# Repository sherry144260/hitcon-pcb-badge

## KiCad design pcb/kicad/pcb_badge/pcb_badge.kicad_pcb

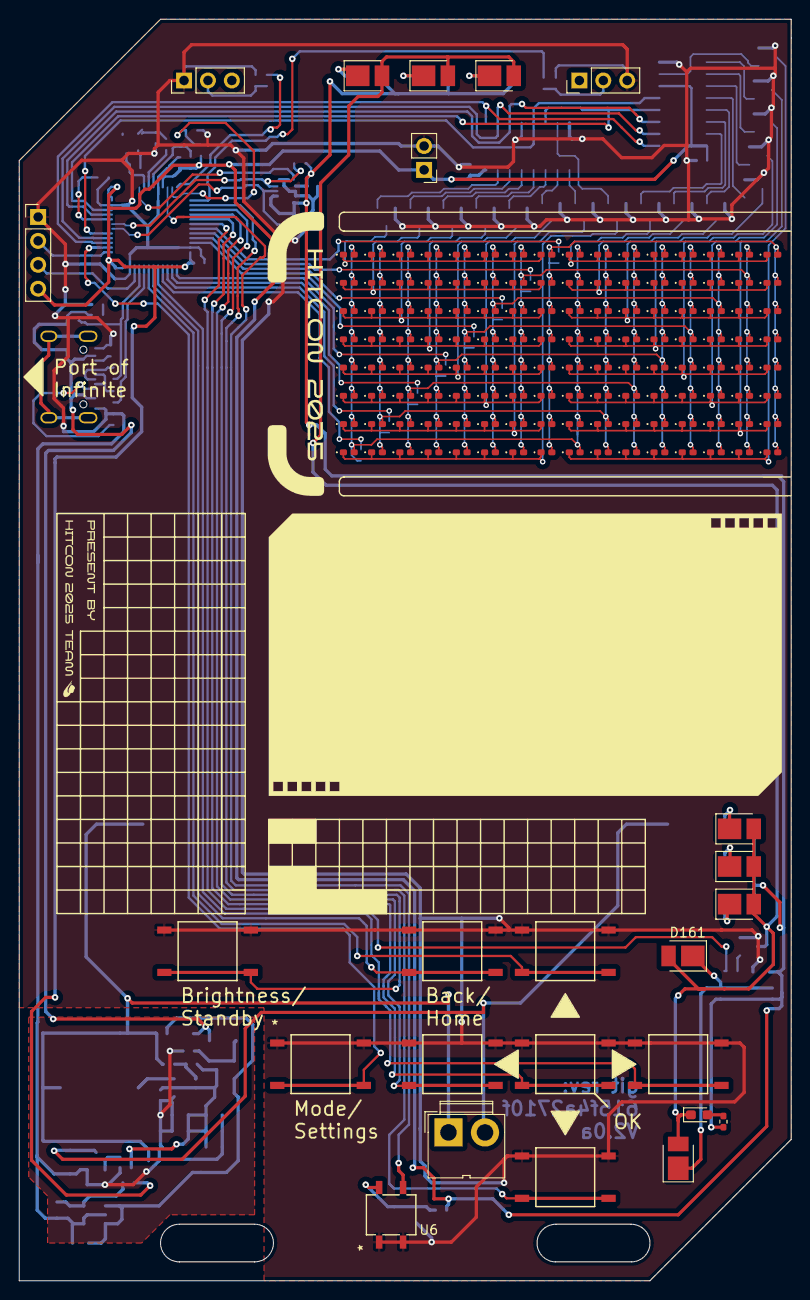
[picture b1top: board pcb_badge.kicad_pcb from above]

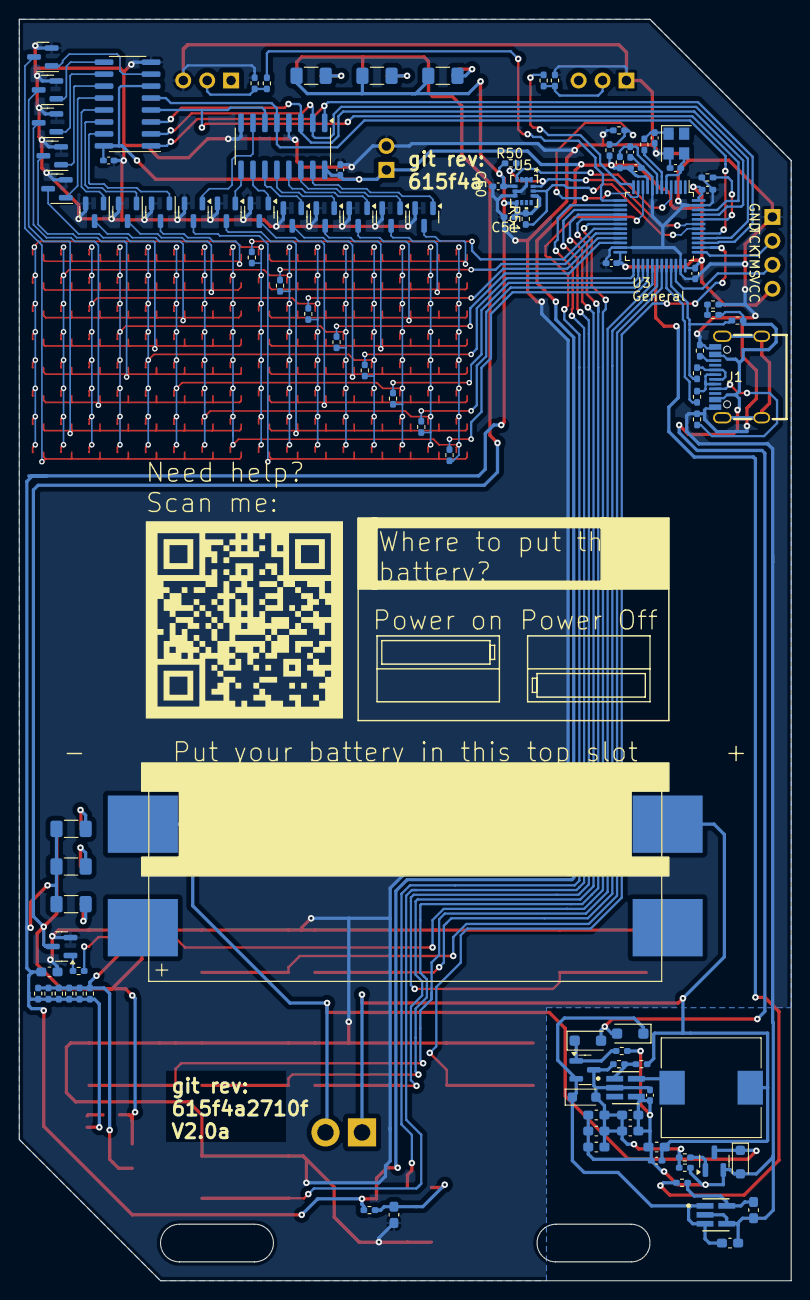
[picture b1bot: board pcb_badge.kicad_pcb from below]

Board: 2 copper layers, 82.0 x 134.0 mm, 254 parts (102 on the bottom side), 108 nets.

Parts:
BT1: BAT_2; BH-AAA-B5AK001
C1, C21, C30, C31, C32, C33, C40, C50, C51, C80: 0.1u; C_0402_1005Metric_Pad0.74x0.62mm_HandSolder
C10, C11: 1u; C_0603_1608Metric_Pad1.08x0.95mm_HandSolder
C20, C22, C23, C24, C25, C26, C92: 10u; C_0603_1608Metric_Pad1.08x0.95mm_HandSolder
C34: NC; C_0402_1005Metric_Pad0.74x0.62mm_HandSolder
C37, C38: 20p; C_0402_1005Metric_Pad0.74x0.62mm_HandSolder
C60: 4.7u; C_0603_1608Metric_Pad1.08x0.95mm_HandSolder
D00, D01, D02, D03, D04, D05, D06, D07, D10, D11, D12, D13, D14, D15, D16, D17, D20, D21, D22, D23, D24, D25, D26, D27, D30, D31, D32, D33, D34, D35, D36, D37, D40, D41, D42, D43, D44, D45, D46, D47, D50, D51, D52, D53, D54, D55, D56, D57, D60, D61, D62, D63, D64, D65, D66, D67, D70, D71, D72, D73, D74, D75, D76, D77, D80, D81, D82, D83, D84, D85, D86, D87, D90, D91, D92, D93, D94, D95, D96, D97, D100, D101, D102, D103, D104, D105, D106, D107, D110, D111, D112, D113, D114, D115, D116, D117, D120, D121, D122, D123, D124, D125, D126, D127, D130, D131, D132, D133, D134, D135, D136, D137, D140, D141, D142, D143, D144, D145, D146, D147, D150, D151, D152, D153, D154, D155, D156, D157: LED; LED_0402_1005Metric_Pad0.77x0.64mm_HandSolder
D1: NC; D_SOD-323_HandSoldering
D2, D18: SOD4007-MS; D_SOD-123F
D3: NC; LED_0603_1608Metric_Pad1.05x0.95mm_HandSolder
D9: NSR0320MW2T1G; D_SOD-323_HandSoldering
D160, D162, D163, D164, D165, D166, D167: NC; LED_PLCC_2835_Handsoldering
D161: NEWOPTO XYC-IRA2835A90-X4; LED_PLCC_2835_Handsoldering
J1: DEALON USB-TYPE-C-018
J2: Conn_01x02_Pin; JWT_A3963_1x02_P3.96mm_Vertical
J3: Conn_01x04_Pin; PinHeader_1x04_P2.54mm_Vertical
J4, J5: Conn_01x03_Pin; PinHeader_1x03_P2.54mm_Vertical
J7: Conn_01x02_Pin; PinHeader_1x02_P2.54mm_Vertical
L20: CYL104R-33UH; L_10.4x10.4_H4.8
Q1: SI2302; SOT-23
Q2: JSM2301S; SOT-23
Q9, Q90, Q91, Q92, Q93, Q94, Q95, Q96, Q97, Q98, Q99, Q910, Q911, Q912, Q913, Q914, Q915: 2N7002; SOT-23
R1, R2: 20R; R_0402_1005Metric_Pad0.72x0.64mm_HandSolder
R3, R20, R50, R51: 4.7k; R_0402_1005Metric_Pad0.72x0.64mm_HandSolder
R4, R11: 8.2M; R_0402_1005Metric_Pad0.72x0.64mm_HandSolder
R5, R6, R7, R17, R18, R19: 100k; R_0402_1005Metric_Pad0.72x0.64mm_HandSolder
R8, R9, R21, R31, R32, R33, R34: 470; R_0402_1005Metric_Pad0.72x0.64mm_HandSolder
R10, R23: 0; R_0402_1005Metric_Pad0.72x0.64mm_HandSolder
R14: 220; R_0402_1005Metric_Pad0.72x0.64mm_HandSolder
R16: 33k; R_0402_1005Metric_Pad0.72x0.64mm_HandSolder
R22, R29, R30, R35, R36: NC; R_0402_1005Metric_Pad0.72x0.64mm_HandSolder
R24, R25: 5.1k; R_0402_1005Metric_Pad0.72x0.64mm_HandSolder
R61: 100; R_0402_1005Metric_Pad0.72x0.64mm_HandSolder
R90, R91, R92, R93, R94, R95, R96, R97: 300; R_0402_1005Metric_Pad0.72x0.64mm_HandSolder
R162, R163, R164, R165, R166, R167: 110R; R_1206_3216Metric_Pad1.30x1.75mm_HandSolder
SW1, SW2, SW3, SW4, SW5, SW6, SW7, SW8: SW_MEC_5E; SOIC4_TL3301SPF160RGTAPE_EWI
U1: TLV70328DBVR; SOT-23-5
U2: QX2304L33F; SOT-23-5
U3: STM32F103CBT6; LQFP-48_7x7mm_P0.5mm
U4, U8: 74HC238; SOP-16_3.9x9.9mm_P1.27mm
U5: LSM6DS3TR-C; QFN_S3TR-C_STM
U6: IRM-H638T/TR2; IRM-H638T
Y1: TAXM8M4RFDCET2T; Oscillator_SMD_Abracon_ASE-4Pin_3.2x2.5mm

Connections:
/LED Matrix2/MAT_RJ: D80.1 (K), D81.1 (K), D82.1 (K), D83.1 (K), D84.1 (K), D85.1 (K), D86.1 (K), D87.1 (K), Q98.3 (D)
/LED Matrix2/MAT_RK: D90.1 (K), D91.1 (K), D92.1 (K), D93.1 (K), D94.1 (K), D95.1 (K), D96.1 (K), D97.1 (K), Q99.3 (D)
/LED Matrix2/MAT_RL: D100.1 (K), D101.1 (K), D102.1 (K), D103.1 (K), D104.1 (K), D105.1 (K), D106.1 (K), D107.1 (K), Q910.3 (D)
/LED Matrix2/MAT_RM: D110.1 (K), D111.1 (K), D112.1 (K), D113.1 (K), D114.1 (K), D115.1 (K), D116.1 (K), D117.1 (K), Q911.3 (D)
/LED Matrix2/MAT_RN: D120.1 (K), D121.1 (K), D122.1 (K), D123.1 (K), D124.1 (K), D125.1 (K), D126.1 (K), D127.1 (K), Q912.3 (D)
/LED Matrix2/MAT_RP: D130.1 (K), D131.1 (K), D132.1 (K), D133.1 (K), D134.1 (K), D135.1 (K), D136.1 (K), D137.1 (K), Q913.3 (D)
/LED Matrix2/MAT_RQ: D140.1 (K), D141.1 (K), D142.1 (K), D143.1 (K), D144.1 (K), D145.1 (K), D146.1 (K), D147.1 (K), Q914.3 (D)
/LED Matrix2/MAT_RR: D150.1 (K), D151.1 (K), D152.1 (K), D153.1 (K), D154.1 (K), D155.1 (K), D156.1 (K), D157.1 (K), Q915.3 (D)
/LED Matrix2/Y8D: Q98.1 (G), U8.15 (Y0)
/LED Matrix2/Y9D: Q99.1 (G), U8.14 (Y1)
/LED Matrix2/Y10D: Q910.1 (G), U8.13 (Y2)
/LED Matrix2/Y11D: Q911.1 (G), U8.12 (Y3)
/LED Matrix2/Y12D: Q912.1 (G), U8.11 (Y4)
/LED Matrix2/Y13D: Q913.1 (G), U8.10 (Y5)
/LED Matrix2/Y14D: Q914.1 (G), U8.9 (Y6)
/LED Matrix2/Y15D: Q915.1 (G), U8.7 (Y7)
/LED Matrix/A0: U3.39 (PB3), U4.1 (A0), U8.1 (A0)
/LED Matrix/A1: U3.40 (PB4), U4.2 (A1), U8.2 (A1)
/LED Matrix/A2: U3.45 (PB8), U4.3 (A2), U8.3 (A2)
/LED Matrix/A3: U3.46 (PB9), U4.4 (~E1), U8.6 (E3)
/LED Matrix/DEC_EN: U3.41 (PB5), U4.5 (~E2), U8.5 (~E2)
/LED Matrix/MAT_CA: D00.2 (A), D10.2 (A), D20.2 (A), D30.2 (A), D40.2 (A), D50.2 (A), D60.2 (A), D70.2 (A), D80.2 (A), D90.2 (A), D100.2 (A), D110.2 (A), D120.2 (A), D130.2 (A), D140.2 (A), D150.2 (A), R90.2
/LED Matrix/MAT_CB: D01.2 (A), D11.2 (A), D21.2 (A), D31.2 (A), D41.2 (A), D51.2 (A), D61.2 (A), D71.2 (A), D81.2 (A), D91.2 (A), D101.2 (A), D111.2 (A), D121.2 (A), D131.2 (A), D141.2 (A), D151.2 (A), R91.2
/LED Matrix/MAT_CC: D02.2 (A), D12.2 (A), D22.2 (A), D32.2 (A), D42.2 (A), D52.2 (A), D62.2 (A), D72.2 (A), D82.2 (A), D92.2 (A), D102.2 (A), D112.2 (A), D122.2 (A), D132.2 (A), D142.2 (A), D152.2 (A), R92.2
/LED Matrix/MAT_CD: D03.2 (A), D13.2 (A), D23.2 (A), D33.2 (A), D43.2 (A), D53.2 (A), D63.2 (A), D73.2 (A), D83.2 (A), D93.2 (A), D103.2 (A), D113.2 (A), D123.2 (A), D133.2 (A), D143.2 (A), D153.2 (A), R93.2
/LED Matrix/MAT_CE: D04.2 (A), D14.2 (A), D24.2 (A), D34.2 (A), D44.2 (A), D54.2 (A), D64.2 (A), D74.2 (A), D84.2 (A), D94.2 (A), D104.2 (A), D114.2 (A), D124.2 (A), D134.2 (A), D144.2 (A), D154.2 (A), R94.2
/LED Matrix/MAT_CF: D05.2 (A), D15.2 (A), D25.2 (A), D35.2 (A), D45.2 (A), D55.2 (A), D65.2 (A), D75.2 (A), D85.2 (A), D95.2 (A), D105.2 (A), D115.2 (A), D125.2 (A), D135.2 (A), D145.2 (A), D155.2 (A), R95.2
/LED Matrix/MAT_CG: D06.2 (A), D16.2 (A), D26.2 (A), D36.2 (A), D46.2 (A), D56.2 (A), D66.2 (A), D76.2 (A), D86.2 (A), D96.2 (A), D106.2 (A), D116.2 (A), D126.2 (A), D136.2 (A), D146.2 (A), D156.2 (A), R96.2
/LED Matrix/MAT_CH: D07.2 (A), D17.2 (A), D27.2 (A), D37.2 (A), D47.2 (A), D57.2 (A), D67.2 (A), D77.2 (A), D87.2 (A), D97.2 (A), D107.2 (A), D117.2 (A), D127.2 (A), D137.2 (A), D147.2 (A), D157.2 (A), R97.2
/LED Matrix/MAT_RA: D00.1 (K), D01.1 (K), D02.1 (K), D03.1 (K), D04.1 (K), D05.1 (K), D06.1 (K), D07.1 (K), Q90.3 (D)
/LED Matrix/MAT_RB: D10.1 (K), D11.1 (K), D12.1 (K), D13.1 (K), D14.1 (K), D15.1 (K), D16.1 (K), D17.1 (K), Q91.3 (D)
/LED Matrix/MAT_RC: D20.1 (K), D21.1 (K), D22.1 (K), D23.1 (K), D24.1 (K), D25.1 (K), D26.1 (K), D27.1 (K), Q92.3 (D)
/LED Matrix/MAT_RD: D30.1 (K), D31.1 (K), D32.1 (K), D33.1 (K), D34.1 (K), D35.1 (K), D36.1 (K), D37.1 (K), Q93.3 (D)
/LED Matrix/MAT_RE: D40.1 (K), D41.1 (K), D42.1 (K), D43.1 (K), D44.1 (K), D45.1 (K), D46.1 (K), D47.1 (K), Q94.3 (D)
/LED Matrix/MAT_RF: D50.1 (K), D51.1 (K), D52.1 (K), D53.1 (K), D54.1 (K), D55.1 (K), D56.1 (K), D57.1 (K), Q95.3 (D)
/LED Matrix/MAT_RG: D60.1 (K), D61.1 (K), D62.1 (K), D63.1 (K), D64.1 (K), D65.1 (K), D66.1 (K), D67.1 (K), Q96.3 (D)
/LED Matrix/MAT_RH: D70.1 (K), D71.1 (K), D72.1 (K), D73.1 (K), D74.1 (K), D75.1 (K), D76.1 (K), D77.1 (K), Q97.3 (D)
/LED Matrix/Y0D: Q90.1 (G), U4.15 (Y0)
/LED Matrix/Y1D: Q91.1 (G), U4.14 (Y1)
/LED Matrix/Y2D: Q92.1 (G), U4.13 (Y2)
/LED Matrix/Y3D: Q93.1 (G), U4.12 (Y3)
/LED Matrix/Y4D: Q94.1 (G), U4.11 (Y4)
/LED Matrix/Y5D: Q95.1 (G), U4.10 (Y5)
/LED Matrix/Y6D: Q96.1 (G), U4.9 (Y6)
/LED Matrix/Y7D: Q97.1 (G), U4.7 (Y7)
/MCU/ACC_INT1: U3.4 (PC15), U5.4 (INT1)
/MCU/BOOT0: R20.2, U3.44 (BOOT0)
/MCU/BTN_A: SW1.3 (K), SW1.4 (A), U3.38 (PA15)
/MCU/BTN_B: SW2.3 (K), SW2.4 (A), U3.14 (PA4)
/MCU/BTN_C: SW3.3 (K), SW3.4 (A), U3.15 (PA5)
/MCU/BTN_D: SW4.3 (K), SW4.4 (A), U3.16 (PA6)
/MCU/BTN_E: SW5.3 (K), SW5.4 (A), U3.17 (PA7)
/MCU/BTN_F: SW6.3 (K), SW6.4 (A), U3.29 (PA8)
/MCU/BTN_G: SW7.3 (K), SW7.4 (A), U3.30 (PA9)
/MCU/BTN_H: SW8.3 (K), SW8.4 (A), U3.31 (PA10)
/MCU/CA: R90.1, U3.28 (PB15)
/MCU/CB: R91.1, U3.27 (PB14)
/MCU/CC: R92.1, U3.26 (PB13)
/MCU/CD: R93.1, U3.25 (PB12)
/MCU/CE: R94.1, U3.22 (PB11)
/MCU/CF: R95.1, U3.21 (PB10)
/MCU/CG: R96.1, U3.20 (PB2)
/MCU/CH: R97.1, U3.19 (PB1)
/MCU/I2C1_SCL: R51.1, U3.42 (PB6), U5.13 (SCL)
/MCU/I2C1_SDA: R50.1, U3.43 (PB7), U5.14 (SDA)
/MCU/IRDRV: R14.1, U3.18 (PB0)
/MCU/IRDRV_G: Q9.1 (G), R14.2
/MCU/IRD_M1: D160.1 (K), D161.1 (K), R31.2, R32.2, R33.2, R34.2, R35.2, R36.2
/MCU/IRD_M2: D3.2 (A), R29.2
/MCU/IRD_M3: D162.1 (K), R162.2
/MCU/IRD_M4: D163.1 (K), R163.2
/MCU/IRD_M5: D164.1 (K), R164.2
/MCU/IRD_M6: D165.1 (K), R165.2
/MCU/IRD_M7: D166.1 (K), R166.2
/MCU/IRD_M8: D167.1 (K), R167.2
/MCU/IRD_N: D3.1 (K), D160.2 (A), D161.2 (A), D162.2 (A), D163.2 (A), D164.2 (A), D165.2 (A), D166.2 (A), D167.2 (A), Q9.3 (D)
/MCU/IRRX: U3.10 (PA0), U6.3 (OUTPUT)
/MCU/NOISE_IN: R4.2, R11.1, U3.11 (PA1)
/MCU/OSC_IN: C38.1, U3.5 (PD0), Y1.3 (OUT)
/MCU/OSC_OUT: R21.1, U3.6 (PD1)
/MCU/OSC_OUT_R: C37.1, R21.2, Y1.1 (EN)
/MCU/PA2: R8.2, U3.12 (PA2)
/MCU/PA3: R9.2, U3.13 (PA3)
/MCU/PA11: R1.2, U3.32 (PA11)
/MCU/PA12: R2.2, R3.1, U3.33 (PA12)
/MCU/PA13: J3.3, U3.34 (PA13)
/MCU/PA14: J3.2, U3.37 (PA14)
/MCU/USB_DET: R16.2, R17.1
/Power/AAA_NEG: BT1.2 (-), D9.1 (K), J2.2, Q1.3 (D)
/Power/AAA_POS: BT1.1 (+), C1.1, C20.1, J2.1, L20.1, R22.1
/Power/BOOST_LX: L20.2, U2.5 (LX)
/Power/BOOST_MIX_GATE: D18.1 (K), Q2.1 (G), R5.1
/Power/BOOST_OUT: C21.1, C22.1, C23.1, C24.1, C25.1, C26.1, D1.2 (A), Q2.3 (D), R18.2, R19.1, R23.1, U2.2 (OUT)
/Power/PWR_IN_MIXED: C10.2, D1.1 (K), D2.1 (K), Q2.2 (S), U1.1 (IN), U1.3 (EN)
/Power/RP_PROT_GATE: Q1.1 (G), R18.1
/Power/TLV_OUT: C11.1, R10.1, U1.5 (OUT)
/Power/USB_5V: D2.2 (A), D18.2 (A), J1.A4 (VBUS), J1.A9 (VBUS), J1.B4 (VBUS), J1.B9 (VBUS), R3.2, R16.1
/Power/USB_DM_RAW: J1.A7 (D-), J1.B7 (D-), R1.1
/Power/USB_DP_RAW: J1.A6 (D+), J1.B6 (D+), R2.1
GND: C1.2, C10.1, C11.2, C20.2, C21.2, C22.2, C23.2, C24.2, C25.2, C26.2, C30.2, C31.2, C32.2, C33.2, C34.2, C37.2, C38.2, C40.2, C50.2, C51.2, C60.2, C80.2, C92.2, D9.2 (A), J1.A1 (GND), J1.A12 (GND), J1.B1 (GND), J1.B12 (GND), J3.1, J4.1, J5.3, J7.2, Q1.2 (S), Q9.2 (S), Q90.2 (S), Q91.2 (S), Q92.2 (S), Q93.2 (S), Q94.2 (S), Q95.2 (S), Q96.2 (S), Q97.2 (S), Q98.2 (S), Q99.2 (S), Q910.2 (S), Q911.2 (S), Q912.2 (S), Q913.2 (S), Q914.2 (S), Q915.2 (S), R5.2, R6.2, R7.2, R11.2, R17.2, R19.2, R20.1, R24.2, R25.2, SW1.1, SW1.2, SW2.1, SW2.2, SW3.1, SW3.2, SW4.1, SW4.2, SW5.1, SW5.2, SW6.1, SW6.2, SW7.1, SW7.2, SW8.1, SW8.2, U1.2 (GND), U1.4 (NC), U2.4 (GND), U3.8 (VSSA), U3.23 (VSS), U3.35 (VSS), U3.47 (VSS), U4.8 (GND), U5.1 (SDO/SA0), U5.2 (SDx), U5.3 (SCx), U5.6 (GND), U5.7 (GND), U6.1 (GND), U6.2 (GND), U8.4 (~E1), U8.8 (GND), Y1.2 (GND)
unnamed: J1.A5 (CC1), R25.1
unnamed: J1.B5 (CC2), R24.1
unnamed: J4.2, R6.1, R8.1
unnamed: J5.2, R7.1, R9.1
unnamed: R22.2, R23.2, U2.1 (EN)
unnamed: C34.1, R30.2, U3.7 (NRST)
unnamed: C60.1, R61.1, U6.4 (VCC)
VCC: C30.1, C31.1, C32.1, C33.1, C40.1, C50.1, C51.1, C80.1, C92.1, J3.4, J7.1, R4.1, R10.2, R29.1, R30.1, R31.1, R32.1, R33.1, R34.1, R35.1, R36.1, R50.2, R51.2, R61.2, R162.1, R163.1, R164.1, R165.1, R166.1, R167.1, U3.9 (VDDA), U3.24 (VDD), U3.36 (VDD), U3.48 (VDD), U4.6 (E3), U4.16 (VCC), U5.5 (VDDIO), U5.8 (VDD), U5.12 (CS), U8.16 (VCC)

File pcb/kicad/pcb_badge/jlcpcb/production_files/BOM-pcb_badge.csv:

Comment,Designator,Footprint,LCSC
8.2M,"R11,R4",R_0402_1005Metric_Pad0.72x0.64mm_HandSolder,C103174
110R,"R165,R166,R167",R_1206_3216Metric_Pad1.30x1.75mm_HandSolder,C1450
0.1u,"C1,C21,C30,C31,C32,C33,C40,C50,C51,C80",C_0402_1005Metric_Pad0.74x0.62mm_HandSolder,C1525
1u,"C10,C11",C_0603_1608Metric_Pad1.08x0.95mm_HandSolder,C152900
20p,"C37,C38",C_0402_1005Metric_Pad0.74x0.62mm_HandSolder,C1554
110R,"R162,R163",R_1206_3216Metric_Pad1.30x1.75mm_HandSolder,C159726
4.7u,C60,C_0603_1608Metric_Pad1.08x0.95mm_HandSolder,C1705
10u,"C20,C22,C23,C24,C25,C26,C92",C_0603_1608Metric_Pad1.08x0.95mm_HandSolder,C19702
20R,"R1,R2",R_0402_1005Metric_Pad0.72x0.64mm_HandSolder,C203133
QX2304L33F,U2,SOT-23-5,C219039
100,R61,R_0402_1005Metric_Pad0.72x0.64mm_HandSolder,C25076
220,R14,R_0402_1005Metric_Pad0.72x0.64mm_HandSolder,C25091
300,"R90,R91,R92,R93,R94,R95,R96,R97",R_0402_1005Metric_Pad0.72x0.64mm_HandSolder,C25102
470,"R21,R31,R32,R33,R34,R8,R9",R_0402_1005Metric_Pad0.72x0.64mm_HandSolder,C25117
SW_MEC_5E,"SW1,SW2,SW3,SW4,SW5,SW6,SW7,SW8",SOIC4_TL3301SPF160RGTAPE_EWI,C255812
100k,"R17,R18,R19,R5,R6,R7",R_0402_1005Metric_Pad0.72x0.64mm_HandSolder,C25741
33k,R16,R_0402_1005Metric_Pad0.72x0.64mm_HandSolder,C25779
4.7k,"R20,R3,R50,R51",R_0402_1005Metric_Pad0.72x0.64mm_HandSolder,C25900
5.1k,"R24,R25",R_0402_1005Metric_Pad0.72x0.64mm_HandSolder,C25905
TLV70328DBVR,U1,SOT-23-5,C2867699
CYL104R-33UH,L20,L_10.4x10.4_H4.8,C2879699
Conn_01x03_Pin,J4,PinHeader_1x03_P2.54mm_Vertical,C2894945
Conn_01x03_Pin,J5,PinHeader_1x03_P2.54mm_Vertical,C2897385
DEALON USB-TYPE-C-018,J1,DEALON USB-TYPE-C-018,C2927038
110R,R164,R_1206_3216Metric_Pad1.30x1.75mm_HandSolder,C2934192
SOD4007-MS,"D18,D2",D_SOD-123F,C3008061
TAXM8M4RFDCET2T,Y1,Oscillator_SMD_Abracon_ASE-4Pin_3.2x2.5mm,C403948
SI2302,Q1,SOT-23,C4748714
2N7002,"Q9,Q90,Q91,Q910,Q911,Q912,Q913,Q914,Q915,Q92,Q93,Q94,Q95,Q96,Q97,Q98,Q99",SOT-23,C4748728
NSR0320MW2T1G,D9,D_SOD-323_HandSoldering,C48192
74HC238,"U4,U8",SOP-16_3.9x9.9mm_P1.27mm,C5379113
0,"R10,R23",R_0402_1005Metric_Pad0.72x0.64mm_HandSolder,C60485
NEWOPTO XYC-IRA2835A90-X4,D161,LED_PLCC_2835_Handsoldering,C6081290
STM32F103CBT6,U3,LQFP-48_7x7mm_P0.5mm,C8304
IRM-H638T/TR2,U6,IRM-H638T,C91447
JSM2301S,Q2,SOT-23,C916399
BAT_2,BT1,BH-AAA-B5AK001,C964881
LED,"D00,D01,D02,D03,D04,D05,D06,D07,D10,D100,D101,D102,D103,D104,D105,D106,D107,D11,D110,D111,D112,D113,D114,D115,D116,D117,D12,D120,D121,D122,D123,D124,D125,D126,D127,D13,D130,D131,D132,D133,D134,D135,D136,D137,D14,D140,D141,D142,D143,D144,D145,D146,D147,D15,D150,D151,D152,D153,D154,D155,D156,D157,D16,D17,D20,D21,D22,D23,D24,D25,D26,D27,D30,D31,D32,D33,D34,D35,D36,D37,D40,D41,D42,D43,D44,D45,D46,D47,D50,D51,D52,D53,D54,D55,D56,D57,D60,D61,D62,D63,D64,D65,D66,D67,D70,D71,D72,D73,D74,D75,D76,D77,D80,D81,D82,D83,D84,D85,D86,D87,D90,D91,D92,D93,D94,D95,D96,D97",LED_0402_1005Metric_Pad0.77x0.64mm_HandSolder,C965790
LSM6DS3TR-C,U5,QFN_S3TR-C_STM,C967633
NC,D160,LED_PLCC_2835_Handsoldering,
Conn_01x02_Pin,J7,PinHeader_1x02_P2.54mm_Vertical,
NC,D3,LED_0603_1608Metric_Pad1.05x0.95mm_HandSolder,
Conn_01x04_Pin,J3,PinHeader_1x04_P2.54mm_Vertical,
NC,R29,R_0402_1005Metric_Pad0.72x0.64mm_HandSolder,
NC,R36,R_0402_1005Metric_Pad0.72x0.64mm_HandSolder,
NC,R35,R_0402_1005Metric_Pad0.72x0.64mm_HandSolder,
NC,C34,C_0402_1005Metric_Pad0.74x0.62mm_HandSolder,
NC,R22,R_0402_1005Metric_Pad0.72x0.64mm_HandSolder,
NC,D1,D_SOD-323_HandSoldering,
NC,R30,R_0402_1005Metric_Pad0.72x0.64mm_HandSolder,
NC,D164,LED_PLCC_2835_Handsoldering,
NC,D166,LED_PLCC_2835_Handsoldering,
Conn_01x02_Pin,J2,JWT_A3963_1x02_P3.96mm_Vertical,
NC,D163,LED_PLCC_2835_Handsoldering,
NC,D167,LED_PLCC_2835_Handsoldering,
NC,D162,LED_PLCC_2835_Handsoldering,
NC,D165,LED_PLCC_2835_Handsoldering,

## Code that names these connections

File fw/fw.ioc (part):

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Mcu.Name=STM32F103C(8-B)Tx
Mcu.Package=LQFP48
Mcu.UserName=STM32F103CBTx
PA0-WKUP.GPIOParameters=GPIO_Label
PA0-WKUP.GPIO_Label=IrRx
PA0-WKUP.Signal=GPIO_Input
PA1.Signal=ADCx_IN1
PA10.GPIOParameters=GPIO_PuPd,GPIO_Label
PA10.GPIO_Label=BtnH
PA10.GPIO_PuPd=GPIO_PULLUP
PA10.Signal=GPIO_Input
PA11.GPIOParameters=GPIO_Label
PA11.GPIO_Label=UsbDm
PA11.Mode=Device
PA11.Signal=USB_DM
PA12.GPIOParameters=GPIO_Label
PA12.GPIO_Label=UsbDp
PA12.Mode=Device
PA12.Signal=USB_DP
PA13.Mode=Serial_Wire
PA13.Signal=SYS_JTMS-SWDIO
PA14.Mode=Serial_Wire
PA14.Signal=SYS_JTCK-SWCLK
PA15.GPIOParameters=GPIO_PuPd,GPIO_Label
PA15.GPIO_Label=BtnA
PA15.GPIO_PuPd=GPIO_PULLUP
PA15.Signal=GPIO_Input
PA2.Mode=Asynchronous
PA2.Signal=USART2_TX
PA3.Mode=Asynchronous
PA3.Signal=USART2_RX
PA4.GPIOParameters=GPIO_PuPd,GPIO_Label
PA4.GPIO_Label=BtnB
PA4.GPIO_PuPd=GPIO_PULLUP
PA4.Signal=GPIO_Input
PA5.GPIOParameters=GPIO_PuPd,GPIO_Label
PA5.GPIO_Label=BtnC
PA5.GPIO_PuPd=GPIO_PULLUP
PA5.Signal=GPIO_Input
PA6.GPIOParameters=GPIO_PuPd,GPIO_Label
PA6.GPIO_Label=BtnD
PA6.GPIO_PuPd=GPIO_PULLUP
PA6.Signal=GPIO_Input
PA7.GPIOParameters=GPIO_PuPd,GPIO_Label
PA7.GPIO_Label=BtnE
PA7.GPIO_PuPd=GPIO_PULLUP
PA7.Signal=GPIO_Input
PA8.GPIOParameters=GPIO_PuPd,GPIO_Label
PA8.GPIO_Label=BtnF
PA8.GPIO_PuPd=GPIO_PULLUP
PA8.Signal=GPIO_Input
PA9.GPIOParameters=GPIO_PuPd,GPIO_Label
PA9.GPIO_Label=BtnG
PA9.GPIO_PuPd=GPIO_PULLUP
PA9.Signal=GPIO_Input
PB0.GPIOParameters=GPIO_Label
PB0.GPIO_Label=IrTx
PB0.Signal=S_TIM3_CH3
PB1.GPIOParameters=GPIO_Label
PB1.GPIO_Label=LedCh
PB1.Signal=GPIO_Output
PB10.GPIOParameters=GPIO_Label
PB10.GPIO_Label=LedCf
PB10.Signal=GPIO_Output
PB11.GPIOParameters=GPIO_Label
PB11.GPIO_Label=LedCe
PB11.Signal=GPIO_Output
PB12.GPIOParameters=GPIO_Label
PB12.GPIO_Label=LedCd
PB12.Signal=GPIO_Output
PB13.GPIOParameters=GPIO_Label
PB13.GPIO_Label=LedCc
PB13.Signal=GPIO_Output
PB14.GPIOParameters=GPIO_Label
PB14.GPIO_Label=LedCb
PB14.Signal=GPIO_Output
PB15.GPIOParameters=GPIO_Label
PB15.GPIO_Label=LedCa
PB15.Signal=GPIO_Output
PB2.GPIOParameters=GPIO_Label
PB2.GPIO_Label=LedCg
PB2.Signal=GPIO_Output
PB3.GPIOParameters=GPIO_Label
PB3.GPIO_Label=LedA0
PB3.Signal=GPIO_Output
PB4.GPIOParameters=GPIO_Label
PB4.GPIO_Label=LedA1
PB4.Signal=GPIO_Output
PB5.Signal=S_TIM3_CH2
PB6.Mode=I2C
PB6.Signal=I2C1_SCL
PB7.Mode=I2C
PB7.Signal=I2C1_SDA
PB8.GPIOParameters=GPIO_Label
PB8.GPIO_Label=LedA2
PB8.Signal=GPIO_Output
PB9.GPIOParameters=GPIO_Label
PB9.GPIO_Label=LedA3
PB9.Signal=GPIO_Output
PC15-OSC32_OUT.GPIOParameters=GPIO_Label
PC15-OSC32_OUT.GPIO_Label=IMU_INT1
PC15-OSC32_OUT.Signal=GPXTI15
PD0-OSC_IN.Mode=HSE-External-Oscillator
PD0-OSC_IN.Signal=RCC_OSC_IN
PD1-OSC_OUT.Mode=HSE-External-Oscillator
PD1-OSC_OUT.Signal=RCC_OSC_OUT
RCC.SYSCLKFreq_VALUE=48000000
RCC.SYSCLKSource=RCC_SYSCLKSOURCE_PLLCLK
board=custom

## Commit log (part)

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2025-03-11 update secret template
2025-03-11 add calc-num.py
2025-03-11 update gitignore
2025-03-11 add script for generating cache
2025-03-11 change secret.h
2025-03-11 add the script for generating real secret.h
2025-03-11 fix lint
2025-03-16 Define API for EC logic
2025-03-16 refactor: remove 2024 hash game
2025-03-16 base-station: Initial empty classes for base-station
2025-03-16 backend: Add ecc_utils definition
2025-03-16 feat: basic backend api routes
2025-03-16 backend: Empty classes for various big blocks
2025-03-16 feat: check station bearer token
2025-03-16 update: create `IrPacketRequestSchema` for http request
2025-03-16 Add empty backend
2025-03-16 backend: Add configuration
2025-03-16 add accelerometer
    1. change LedA1, A0 pin connection
    2. add I2C1, U5 LSM6DS3TR-C
    3. disconnect USB_DET
2025-03-30 fw: Add CA signature field to pub announce packet
2025-03-30 base-station: Add interface definition between USB serial and basestation
2025-04-13 ECC: first version without testing
2025-04-13 Implement new board graphics design
2025-04-13 add new backend interface
2025-04-20 shrink the signature down to 14 bytes
2025-04-20 fix build errors
2025-04-20 add socre
    schemas - add SoreEntry and ScoreBoard
    app - add get_fake_scores
    backend_interface_new - optimizing
2025-04-20 pcb: Zone fill and pass DRC check
2025-04-20 bugfix and proper verification
2025-04-20 pcb: Added markings on version
2025-05-03 update: packet_processor function signature
2025-05-03 update: return username in verify_packet for ActivityPacket
2025-05-03 fix(PacketProcessor): on_receive_packet
2025-05-03 update: fix tx and acknowledgement
2025-05-03 update: ecc constants
2025-05-03 update: schema
2025-05-03 feat: connect packet_processor to app
2025-05-03 feat: internal methods - packet_hash - get_packet_type - get_user_last_station_uuid
2025-05-03 add test backend packet fake client fake server backend interface packet processor
2025-05-03 add: API for GameLogic to register event handler
2025-05-03 refactor: move CryptoAuth as module instead of layer
2025-05-03 fix: mongo UUID
2025-05-03 feat: handle tx - separate logic of find user station and `send_packet_to_station`
2025-05-03 update: model
2025-05-03 add: placeholder for implement user packet queue
2025-05-03 update: throw exception for unsigned packet
2025-05-03 Add stub for hash service
2025-05-03 fw: Rename username to user in ProximityPacket
2025-05-03 fw: Add documentation on game_data for ActivityPacket
2025-05-03 fw: Add SingleBadgeActivity and SponsorActivity packets
2025-05-03 update: add packet_processor and db to GameLogic
2025-05-03 Rename game_mechanics.md to tower_game_mechanics.md
2025-05-03 feat: packet parsing to event
2025-05-03 update: game logic events follow new schema
2025-05-03 feat: PacketProcessor.event_handler impl
2025-05-07 refactor
2025-05-07 refactor the game logic's structure
2025-05-07 add calculation of station's score
2025-05-11 fw: Add retransmission logic to IrController
2025-05-11 fw: Add signature to SingleBadge event
2025-05-11 fw: Add signature to score announce packet
2025-05-11 update fw.ioc, add IMU_INT1 EXTI
2025-05-11 feat: user queue for packets
2025-05-11 fw: Add GameController for 2025
2025-05-18 fix build errors and renaming
2025-05-18 finish hash service testing
2025-05-18 Untested implementation of the hash service
2025-05-18 fw: Fix IR test failure due to IrData alignment issue
2025-05-18 add a function to get how many times the display has scrolled
2025-05-18 update(backend): schemas
2025-05-18 fix(backend): rx packet saving
2025-05-18 fix(backend): event handler registration
2025-05-18 fix: event handler not registered because game logic controller is not imported
2025-05-18 refactor parse_packet
2025-05-18 refactor: event registration
2025-05-25 fw: Add public key derivation to EcLogic
2025-05-25 fw: Add sending of PubAnnounce IR packet
2025-05-25 fw: Add public key cert in PerBoardData
2025-05-25 hook up hash service with ecc
2025-05-25 DS store bad
2025-05-25 fw: Adjust IrController to recognize hash result struct
2025-06-07 update: parse ttl in IrPacket
2025-06-07 feat(GameLogicController): connect PacketProcessor with GameLogic
2025-06-07 update: add timestamp to event, formalize timestamp to datetime
2025-06-07 fix: remove int timestamp passed to IrPacketObject
2025-06-07 fix(backend): missing import
2025-06-07 feat: parse score from SingleBadgeEvent
2025-06-07 docs: Add packet used for each event
2025-06-07 add Packet Resend Check
2025-06-07 add context manager
2025-06-07 base-station: Merge backend_interface.py
2025-06-07 add the api of two player score
2025-06-07 clean-up
2025-06-07 API in GameController for sending packets via IrController
2025-06-07 Add methods for sending game-related data
2025-06-07 base-station: Translate Chinese comments and messages to English
2025-06-07 base-station: Add pyproject.toml so it will run with uv
2025-06-07 Add aider to gitignore
2025-06-07 fw: Add handling of acknowledgement on pub key announce
2025-06-14 update: add ack scaffold to packet_processor
2025-06-14 feat: two badge activity event
2025-06-14 update: GameActivityEvent schema
2025-06-14 update:(PubAnnounceEvent) check user
2025-06-22 feat: always acking packets, fetch user from CryptoAuth
2025-06-22 update: verify packet in try except
2025-06-22 fix: missing import for UnsignedPacketError
2025-06-22 fix: calculate hash for non-signed packets
2025-06-22 update(ScoreAnnounceEvent): it has signature now
2025-06-22 update(GameActivityEvent): game data has parsed into fields
2025-06-22 feat: MockEcc for testing
2025-06-22 pcb: Add USBDET back to STM32
2025-06-22 feat: mock derive_user_by_pubkey
2025-06-22 fix: push rx to packets
2025-06-25 Update pcb_badge.kicad_sch
    Add resistor value comments for different LED colors
2025-06-25 base-station: Fix integration issue on PubAnnounce with the backend
2025-06-26 Add to menu
2025-06-26 feat: add more character design & add simulator of screen drawing
2025-06-26 refactor: adjust code order for better readability and organization & add some comments
2025-06-26 feat: update pet design, add the component stack method, add anime simulator and example
2025-06-26 doc: change dir / feat: light example screen
2025-06-26 reactor: component stack method / feat: number component
2025-06-26 refactor: change namespace of components / feat: add icon define of numbers
2025-06-26 Create basic framework for Tama App
2025-06-26 feat: cat & dog design and screen demo
2025-06-26 fix: assign PB5 as GPIO_Output
    due to TIM3_CH2 conflict with I2C1
2025-06-26 update fw.ioc and display for accelerometer
    - add i2c1
    - update DisplayService
    - add EXTI IMU_INT1
2025-06-26 Add IMU service and logic
    Implement initialization and self test
    TODO: get step count and INT1 EXTI
2025-06-26 add lsm6ds3tr-c_reg.h from ST
2025-06-26 pcb: Add notes on production with jlc
2025-06-26 Update QRCode to 2025 version
2025-06-27 pcb: Adjust silkscreens to fix DRC
2025-06-27 pcb: Adjust production_notes on confirmation
2025-06-27 pcb: Update SW
    SW1-SW9 C255812 -> C7528752
    Rotation is also updated
2025-06-29 make every ec operations <= 1ms
2025-06-29 Make sign asynchronous
2025-06-29 Add comments to EC contexts
2025-06-29 lint
2025-06-29 fix: compile error in cubeIDE
2025-06-29 ImuLogic add get step function
2025-06-29 Change I2C1 to fast mode
2025-06-29 pcb: Revert Switches
    SW1-SW9 C7528752 -> C255812
    Because the footprint doesn't work.
2025-07-06 different hardware support via preprocessor
    three options:
    - V1_1C
    - V2_0A
    - V2_1BB
2025-07-06 set score after receiving ir packet
2025-07-13 Add proximity routine
2025-07-13 Trigger IRpacket Received if Xboard sendPacket
    Add a Xboard packet callback to let the IRpacketReceived
    func triggered. However, there's a potential vuln that
    should be discussed later.
2025-07-13 Create XBoard Accel Logic to digest IR packet
    Introduce a new feature to accelerate the trans process of
    IR packets. While badges connect to base-station via Xboard,
    it'll send its IR packets via Xboard.
2025-07-13 fw: Add legacy and basestation apps
2025-07-13 fw: Add different XBoard types
2025-07-13 fw: Introduce secure random "feature"
    Will revert if we manage to fix this before the event.
2025-07-13 add Print On Badge packet type
2025-07-13 add background read loop, change dict retrieve to safe method(get)
2025-07-13 Tama: Add basic framework for xboard logic
2025-07-13 Add more XBoard detail
2025-07-13 Fix my_assert
2025-07-13 Add QTE framework
2025-07-18 base-station: Fix packet processor type issue
2025-07-18 base-station: Add display of current score/progress
2025-07-18 Refactor snake game
2025-07-19 Add verification logic of ECC
2025-07-19 fix: align xboard pkt type with base station
2025-07-19 Increase username entropy to max
2025-07-19 fix: halt issue
    * cause: memory leakage
2025-07-19 feat: real dog and cat selection on the board
    * adjusted malloc and free to new and delete
2025-07-19 feat: hatching egg, warning and idle
    * notice:
    1. the feature to get the motion change is not finished yet
    2. the hatching is simulated by button click to adjust the state, need to delete someday
    * bug:
    1. freeze after a period of idle
2025-07-19 feat: the compress method of const icon and the decompress method in runtime (+5 squashed commits)
    Squashed commits:
    [063cea1] feat: compress method of original icon, component and frame
    [389c976] refactor: adjust num icon size and relative things, for future data compress
    [2d32b0a] feat: memory free management & dog/cat idle frame separation
    [1bd7987] feat: dog and cat idle with overview status
    [572652f] refactor: separate simulation part and common part
2025-07-19 refactor: convert dynamic memory allocation to static one (part2, finished)
2025-07-19 feat: add training/battle frame and anime (+3 squashed commits)
    Squashed commits:
    [27bca71] refactor: update image stack usage
    [ad4b5ed] feat: screen of healing of cat and dog
    [9d05fd3] feat: add conditional compiling switch to separate simulation code and real env code
2025-07-19 feat: battle / training and stack_component function relative (+3 squashed commits)
    detail:
    1. battle / training components, stack methods and anime
    2. eliminate feature at stack_component function
    Squashed commits:
    [2719a7e] feat: win lose component and anime / refactor: adjust namespace using method
    [8c6292e] doc: update design drawing
2025-07-19 feat: weak icon and status when idle
2025-07-19 refactor: convert dynamic memory allocation to static one (part1)
2025-07-19 feat: conditional compiling of simulation relative code
2025-07-19 temporary hack to insert per-board private key
2025-07-19 base-station: add packet recorder for TX/RX logging
2025-07-19 Fix snake not starting bug
2025-07-20 fw: Add nonce to single badge score packet
2025-07-20 Add V2.1 RELEASE
2025-07-20 Add Build Configurations
2025-07-20 Add some macro guard for dev build testing
2025-07-20 base-station: Better handling of ir interface TimeoutError
2025-07-20 base-stn: Add response body to debug output
2025-07-20 base-stn: Add packet_log to gitignore
2025-07-20 refactor: decouple RX/TX paths with queues in PacketProcessor
2025-07-20 fix cubeide run configuration
2025-07-20 fw: Add debug app for accelerometer
2025-07-20 fw: Add debug app
2025-07-20 pcb: Added markings on version V2.1dr
2025-07-20 pcb: Generate production files for V2.1br
2025-07-20 pcb: Added markings on version V2.1br
2025-07-20 pcb: Generate production files for V2.1dr
2025-07-20 pcb: Added markings on version V2.1cr
2025-07-20 pcb: Update parts for inventory issue
    R162, R163, R165, R166, R167 -> NC
    J5 C2935993 -> C2897385
2025-07-20 pcb: Adjust text for port of infinity
2025-07-20 pcb: Add power switch for LSM6DS3
2025-07-21 pcb: Add serial current limiting resistor to gate of PMOS for control of LSM6Ds3
    Also update some silkscreen fonts
2025-07-24 Send tama battle score through SendTwoBadgeActivity
2025-07-25 fix: missing break
2025-07-25 refactor: new and delete at simulation part
2025-07-25 refactor: reduce frame data copy
